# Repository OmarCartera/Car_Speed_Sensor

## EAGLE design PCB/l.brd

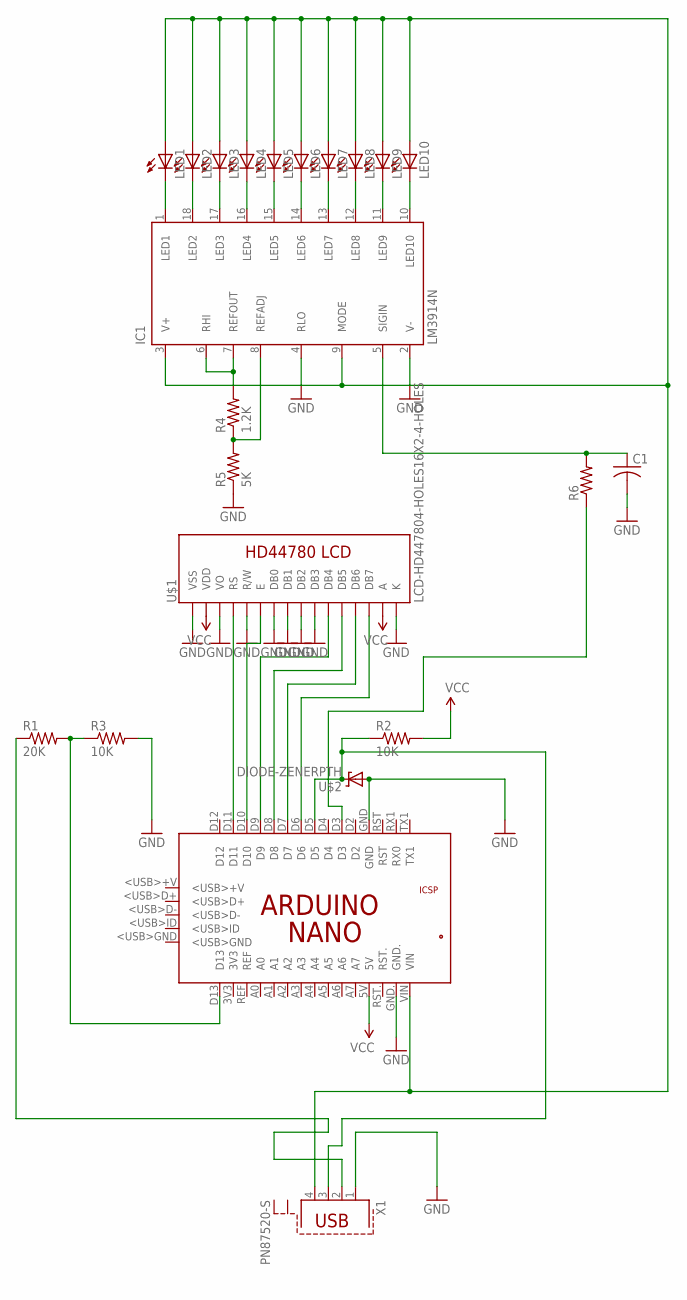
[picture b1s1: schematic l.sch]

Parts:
C1: C-US025-040X050; C025-040X050
IC1: LM3914N; DIL18
LED1, LED2, LED3, LED4, LED5, LED6, LED7, LED8, LED9, LED10: LED5MM
PCB1: ARDUINO_NANO
R1: 20K; 0204/7
R2, R3: 10K; 0204/7
R4: 1.2K; 0204/7
R5: 5K; 0204/7
R6: R-US_0204/7; 0204/7
U$1: LCD-HD447804-HOLES16X2-4-HOLES; LCD-16X2-4HOLES
U$2: DIODE-ZENERPTH; DIODE-ZENER
X1: PN87520-S

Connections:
GND: C1.2, IC1.2 (V-), IC1.4 (RLO), PCB1.GND, PCB1.GND., R3.2, R5.1, U$1.1 (VSS), U$1.3 (VO), U$1.5 (R/W), U$1.7 (DB0), U$1.8 (DB1), U$1.9 (DB2), U$1.10 (DB3), U$1.16 (K), U$2.P$2 (A), X1.1
unnamed: PCB1.D6, U$1.14 (DB7)
unnamed: PCB1.D7, U$1.13 (DB6)
unnamed: PCB1.D8, U$1.12 (DB5)
unnamed: PCB1.D9, U$1.11 (DB4)
unnamed: PCB1.D10, U$1.6 (E)
unnamed: PCB1.D11, U$1.4 (RS)
unnamed: IC1.3 (V+), IC1.9 (MODE), LED1.A, LED2.A, LED3.A, LED4.A, LED5.A, LED6.A, LED7.A, LED8.A, LED9.A, LED10.A, PCB1.VIN, X1.4
unnamed: PCB1.D5, R2.1, U$2.P$1 (C), X1.3
unnamed: PCB1.D13, R1.2, R3.1
unnamed: IC1.1 (LED1), LED1.K (C)
unnamed: R1.1, X1.2
unnamed: IC1.18 (LED2), LED2.K (C)
unnamed: IC1.17 (LED3), LED3.K (C)
unnamed: IC1.16 (LED4), LED4.K (C)
unnamed: IC1.15 (LED5), LED5.K (C)
unnamed: IC1.14 (LED6), LED6.K (C)
unnamed: IC1.13 (LED7), LED7.K (C)
unnamed: IC1.12 (LED8), LED8.K (C)
unnamed: IC1.11 (LED9), LED9.K (C)
unnamed: IC1.10 (LED10), LED10.K (C)
unnamed: IC1.6 (RHI), IC1.7 (REFOUT), R4.2
unnamed: IC1.8 (REFADJ), R4.1, R5.2
unnamed: C1.1, IC1.5 (SIGIN), R6.2
unnamed: PCB1.D3, R6.1
VCC: PCB1.5V, R2.2, U$1.2 (VDD), U$1.15 (A)

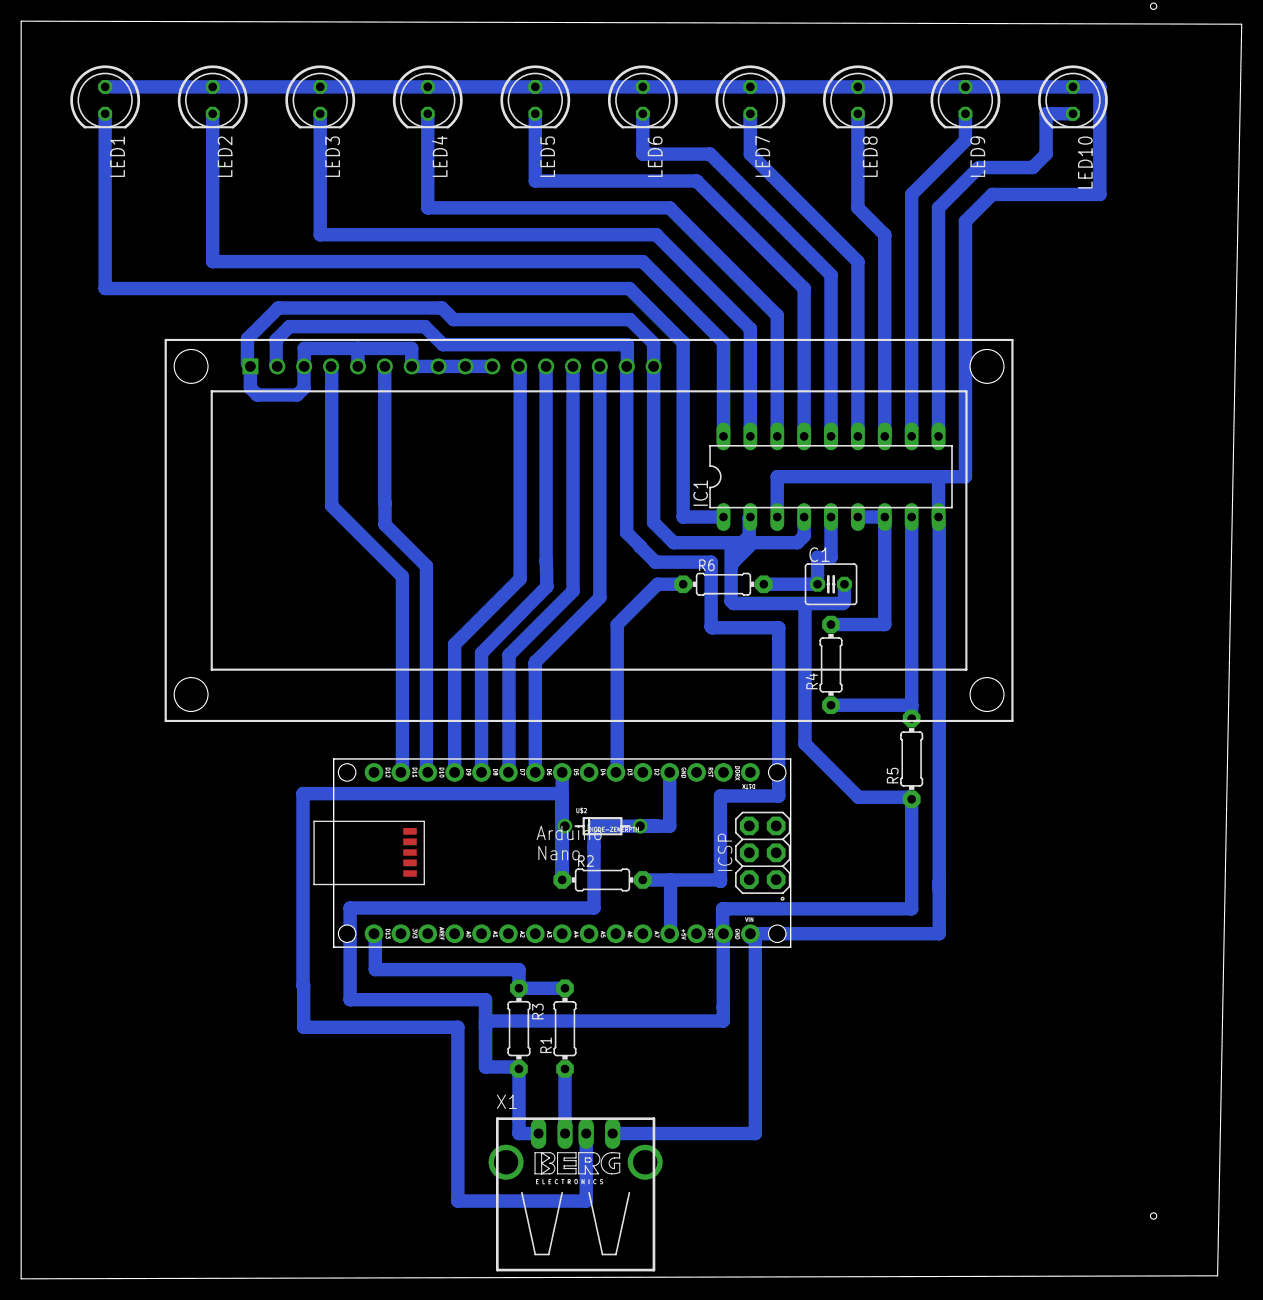
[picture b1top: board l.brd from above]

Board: 2 copper layers, 115.3 x 118.8 mm, 22 parts (0 on the bottom side), 26 nets.

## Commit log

2018-01-14 Rename Final_Shasha.ino to Speed_Sensor.ino
2018-01-14 Create ss
2019-02-12 house keeping

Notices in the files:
parts and their libraries:
SparkFun: Licensing: CC v3.0 Share-Alike You are welcome to use this library for commercial purposes.
